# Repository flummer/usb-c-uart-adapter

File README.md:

# USB-C to TTL-Serial adapter with CP210x

This is just a simpel adapter with USB-C and TTL level UART, plus a few extra IO's. The pinout is designed to fit the 2022 Supercon/2023 Hackaday Berlin badges, and if you want to use the power rails, you need to bridge the corresponsing solder jumpers, they are disconneected by standard and need to be disconnected if used with the badges, as these to pins are used for other things on the badge.

## License

The contents of this repository is released under the following license:

* the "Creative Commons Attribution-ShareAlike 4.0 International License"
  (CC BY-SA 4.0) full text of this license is included in the LICENSE file
  and a copy can also be found at
  [http://creativecommons.org/licenses/by-sa/4.0/](http://creativecommons.org/licenses/by-sa/4.0/)

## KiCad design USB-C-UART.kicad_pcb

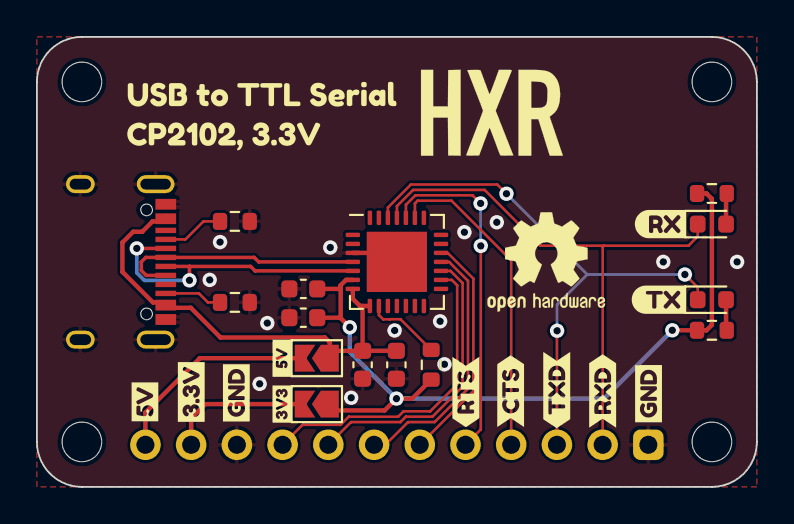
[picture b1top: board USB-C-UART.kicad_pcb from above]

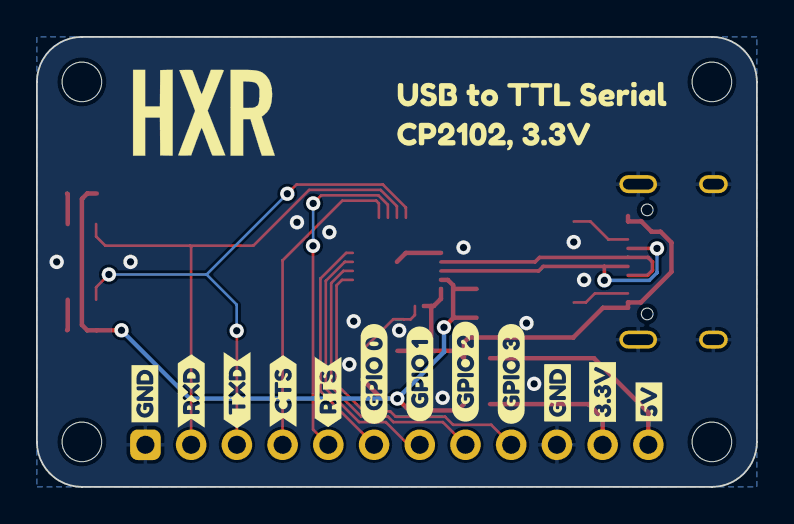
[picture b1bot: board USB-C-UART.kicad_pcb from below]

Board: 2 copper layers, 40.0 x 25.0 mm, 42 parts (14 on the bottom side), 20 nets.

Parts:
C1, C3: 100nF; C_0603_1608Metric
C2, C4: 4.7uF; C_0603_1608Metric
D1: GREEN; LED_0603_1608Metric
D2: RED; LED_0603_1608Metric
J1: USB_C; USB_C_Receptacle_XKB_U262-16XN-4BVC11
J2: Conn_01x12_Socket; PinSocket_1x12_P2.54mm_Horizontal
JP1, JP2: SolderJumper_2_Open; SolderJumper-2_P1.3mm_Open_TrianglePad1.0x1.5mm
R1, R2: 5.1k; R_0603_1608Metric
R3, R4, R5: 1K; R_0603_1608Metric
U1: CP2102N-Axx-xQFN28; QFN-28-1EP_5x5mm_P0.5mm_EP3.35x3.35mm
kibuzzard-6403CC6D: G***; kibuzzard-6403CC6D
kibuzzard-6403CC56: G***; kibuzzard-6403CC56
kibuzzard-6403D5C9: G***; kibuzzard-6403D5C9
kibuzzard-6403D576: G***; kibuzzard-6403D576
kibuzzard-6403DA4F: G***; kibuzzard-6403DA4F
kibuzzard-6403DA5C: G***; kibuzzard-6403DA5C
kibuzzard-6403DA6F: G***; kibuzzard-6403DA6F
kibuzzard-6403DA7C: G***; kibuzzard-6403DA7C
kibuzzard-6403DA55: G***; kibuzzard-6403DA55
kibuzzard-6403DA63: G***; kibuzzard-6403DA63
kibuzzard-6403DA69: G***; kibuzzard-6403DA69
kibuzzard-6403DAA1: G***; kibuzzard-6403DAA1
kibuzzard-6403DAA7: G***; kibuzzard-6403DAA7
kibuzzard-6403DAAD: G***; kibuzzard-6403DAAD
kibuzzard-6403DAB7: G***; kibuzzard-6403DAB7
kibuzzard-6403DABE: G***; kibuzzard-6403DABE
kibuzzard-6403DAC4: G***; kibuzzard-6403DAC4
kibuzzard-6403DAD1: G***; kibuzzard-6403DAD1
kibuzzard-6403EE79: G***; kibuzzard-6403EE79
kibuzzard-6403EEC8: G***; kibuzzard-6403EEC8
kibuzzard-6404B363, kibuzzard-6404B363#2: G***; kibuzzard-6404B363
kibuzzard-6404F9C3: G***; kibuzzard-6404F9C3
kibuzzard-6404F9EF: G***; kibuzzard-6404F9EF
kibuzzard-6404F9F6: G***; kibuzzard-6404F9F6
kibuzzard-6404FA02: G***; kibuzzard-6404FA02

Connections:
+3.3V: C3.1, C4.1, JP2.1 (A), R3.1, R4.1, R5.1, U1.6 (VDD)
/CTS: J2.4, U1.23 (~CTS)
/GPIO_0: J2.6, U1.19 (~TXT/GPIO.0)
/GPIO_1: J2.7, U1.18 (~RXT/GPIO.1)
/GPIO_2: J2.8, U1.17 (RS485/GPIO.2)
/GPIO_3: J2.9, U1.16 (~WAKEUP/GPIO.3)
/RTS: J2.5, U1.24 (~RTS)
/RXD: D1.1 (K), J2.2, U1.25 (RXD)
/TXD: D2.1 (K), J2.3, U1.26 (TXD)
/USB_D+: J1.A6 (D+), J1.B6 (D+), U1.4 (D+)
/USB_D-: J1.A7 (D-), J1.B7 (D-), U1.5 (D-)
GND: C1.2, C2.2, C3.2, C4.2, J1.A1 (GND), J1.A12 (GND), J1.B1 (GND), J1.B12 (GND), J1.S1 (SHIELD), J2.1, J2.10, R1.1, R2.1, U1.3 (GND), U1.29 (GND)
unnamed: D1.2 (A), R4.2
unnamed: D2.2 (A), R5.2
unnamed: J1.A5 (CC1), R1.2
unnamed: J1.B5 (CC2), R2.2
unnamed: J2.11, JP2.2 (B)
unnamed: J2.12, JP1.2 (B)
unnamed: R3.2, U1.9 (~RST)
VBUS: C1.1, C2.1, J1.A4 (VBUS), J1.A9 (VBUS), J1.B4 (VBUS), J1.B9 (VBUS), JP1.1 (A), U1.7 (VREGIN), U1.8 (VBUS)
